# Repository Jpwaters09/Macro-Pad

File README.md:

# Macro Pad

A 12-key macro pad with a configurable rotary encoder and OLED display, built around the RP2354A microcontroller and custom MicroPython firmware. Fully programmable through a web-based configurator.

##

<div style="display: flex">

</div>

##

## How to Use
Plug the Macro Pad into your Windows, Linux, or macOS device using a USB-C data cable, then go to the [Installation Website](https://macropad.jpwaters09.com/Install%20or%20Update) and follow the steps to install (or update) the Macro Pad firmware. This requires a browser that supports Web Serial (Chrome, Edge, Opera, or Firefox), Safari isn't supported.

The OLED display shows the current layer and the function assigned to each key. Press and hold the rotary encoder button to switch layers.

To configure the device (adding, editing, or deleting layers) visit the [Macro Pad Programmer](https://macropad.jpwaters09.com/Configurator).

## Coming Soon
 - A Windows app that will allow you to update and configure settings for the Macro Pad.

## Why I Made This
I built this project to create a fully customisable and open-sourced macro pad. It has also served as a way to develop my skills in schematic design, PCB layout, and 3D Modelling.

## Features
 - USB C
 - 12 macro buttons
 - Rotary encoder with button
 - 128 x 64 OLED display
 - 3D printable housing
 - RP2354A microcontroller
 - 2MB internal flash storage
 - Custom Micropython firmware
 - Multiple programmable layers
 - Web-based configurator (no software install)
 - USB HID compliant (works instantly on any OS)

## Bill Of Materials
|Item                  |Description                                                            |Quantity|Unit Price (£)|Total Price (£) Inc. Tax|URL                                                  |
|----------------------|-----------------------------------------------------------------------|--------|--------------|------------------------|-----------------------------------------------------|
|CL05A104KA5NNNC       |100nF ±10% 25V Ceramic Capacitor X5R 0402                              |100     |$0.0016       |$0.16                   |https://www.lcsc.com/product-detail/C100072.html     |
|CC0402KRX5R5BB103     |10nF ±10% 6.3V Ceramic Capacitor X5R 0402                              |100     |$0.0012       |$0.12                   |https://www.lcsc.com/product-detail/C1853984.html    |
|HGC0805R7106K250NSLJ  |10uF ±10% 25V Ceramic Capacitor X7R 0805                               |5       |$0.1585       |$0.79                   |https://www.lcsc.com/product-detail/C33546010.html       |
|ABM8-272-T3           |±30ppm 10pF ±30ppm SMD3225-4P Crystals RoHS                            |5       |$0.2902       |$1.45                   |https://www.lcsc.com/product-detail/C20625731.html   |
|CL05C150JB5NNNC       |15pF ±5% 50V Ceramic Capacitor C0G 0402                                |100     |$0.0036       |$0.36                   |https://www.lcsc.com/product-detail/C86285.html      |
|FRC0402J102 TS        |1kΩ 62.5mW 50V Thick Film Resistor ±100ppm/℃ ±5% 0402 Chip Resistor   |100     |$0.0008       |$0.08                   |https://www.lcsc.com/product-detail/C2906899.html    |
|RC0402FR-0727RL       |27Ω ±1% 62.5mW 0402 Thick Film Resistor                                |100     |$0.0008       |$0.08                   |https://www.lcsc.com/product-detail/C138021.html     |
|AOTA-B201610S3R3-101-T|2.1A 3.3uH 115mΩ 2.4A Molded Inductor 0806 Fixed Inductors RoHS        |5       |$0.2888       |$1.44                   |https://www.lcsc.com/product-detail/C42411119.html   |
|RAT0233R0FTH          |62.5mW 33Ω 50V Thick Film Resistor ±100ppm/℃ ±1% 0402 Chip Resistor   |100     |$0.0015       |$0.15                   |https://www.lcsc.com/product-detail/C5139599.html    |
|CL05A475KQ5NRNC       |4.7uF ±10% 6.3V Ceramic Capacitor X5R 0402                             |100     |$0.0060       |$0.60                   |https://www.lcsc.com/product-detail/C2932473.html    |
|1RC0402F5101          |5.1kΩ ±1% 62.5mW 0402 Thick Film Resistor                              |100     |$0.0009       |$0.09                   |https://www.lcsc.com/product-detail/C53224182.html   |
|NCP1117ST33T3G        |Linear Voltage Regulator IC Positive Fixed 1 Output 1A SOT-223         |5       |$0.2615       |$1.31                   |https://www.lcsc.com/product-detail/C26537.html      |
|PZ254V-11-04P         |Pin Header 4 Position 2.54mm Pitch Single Row Through Hole -40℃~+105℃|20      |$0.0236       |$0.47                   |https://www.lcsc.com/product-detail/C2691448.html    |
|Rotary Encoder Knob   |22x12mm 6mm D-Type Shaft Hole Knob                                     |1       |$1.6500       |$1.65                   |https://www.aliexpress.com/item/1005011592374989.html|
|SSD1306               |128x64 I2C OLED Display                                                |1       |$0.9900       |$0.99                   |https://www.aliexpress.com/item/1005008995931139.html|
|PEC11R-4225F-S0024    |Plugin Encoders RoHS                                                   |1       |$1.8539       |$1.85                   |https://www.lcsc.com/product-detail/C18198884.html   |
|Cherry MX Keycaps     |Blank black keycap for Cherry MX switches                              |20      |$0.1500       |$3.00                   |https://www.aliexpress.com/item/1005007572331245.html|
|Cherry MX Red Switch  |Cherry MX red 3-pin linear switches                                    |16      |$0.65         |$10.43                  |https://www.aliexpress.com/item/4000100166477.html   |
|RP2354A               |QFN-60(7x7) Microcontrollers RoHS                                      |1       |$1.4615       |$1.46                   |https://www.lcsc.com/product-detail/C41378174.html   |
|2171790001            |USB 2.0 5A 1 16P -40℃~+85℃ SMD USB Connector Assemblies RoHS         |1       |$0.6229       |$0.62                   |https://www.lcsc.com/product-detail/C3197684.html    |

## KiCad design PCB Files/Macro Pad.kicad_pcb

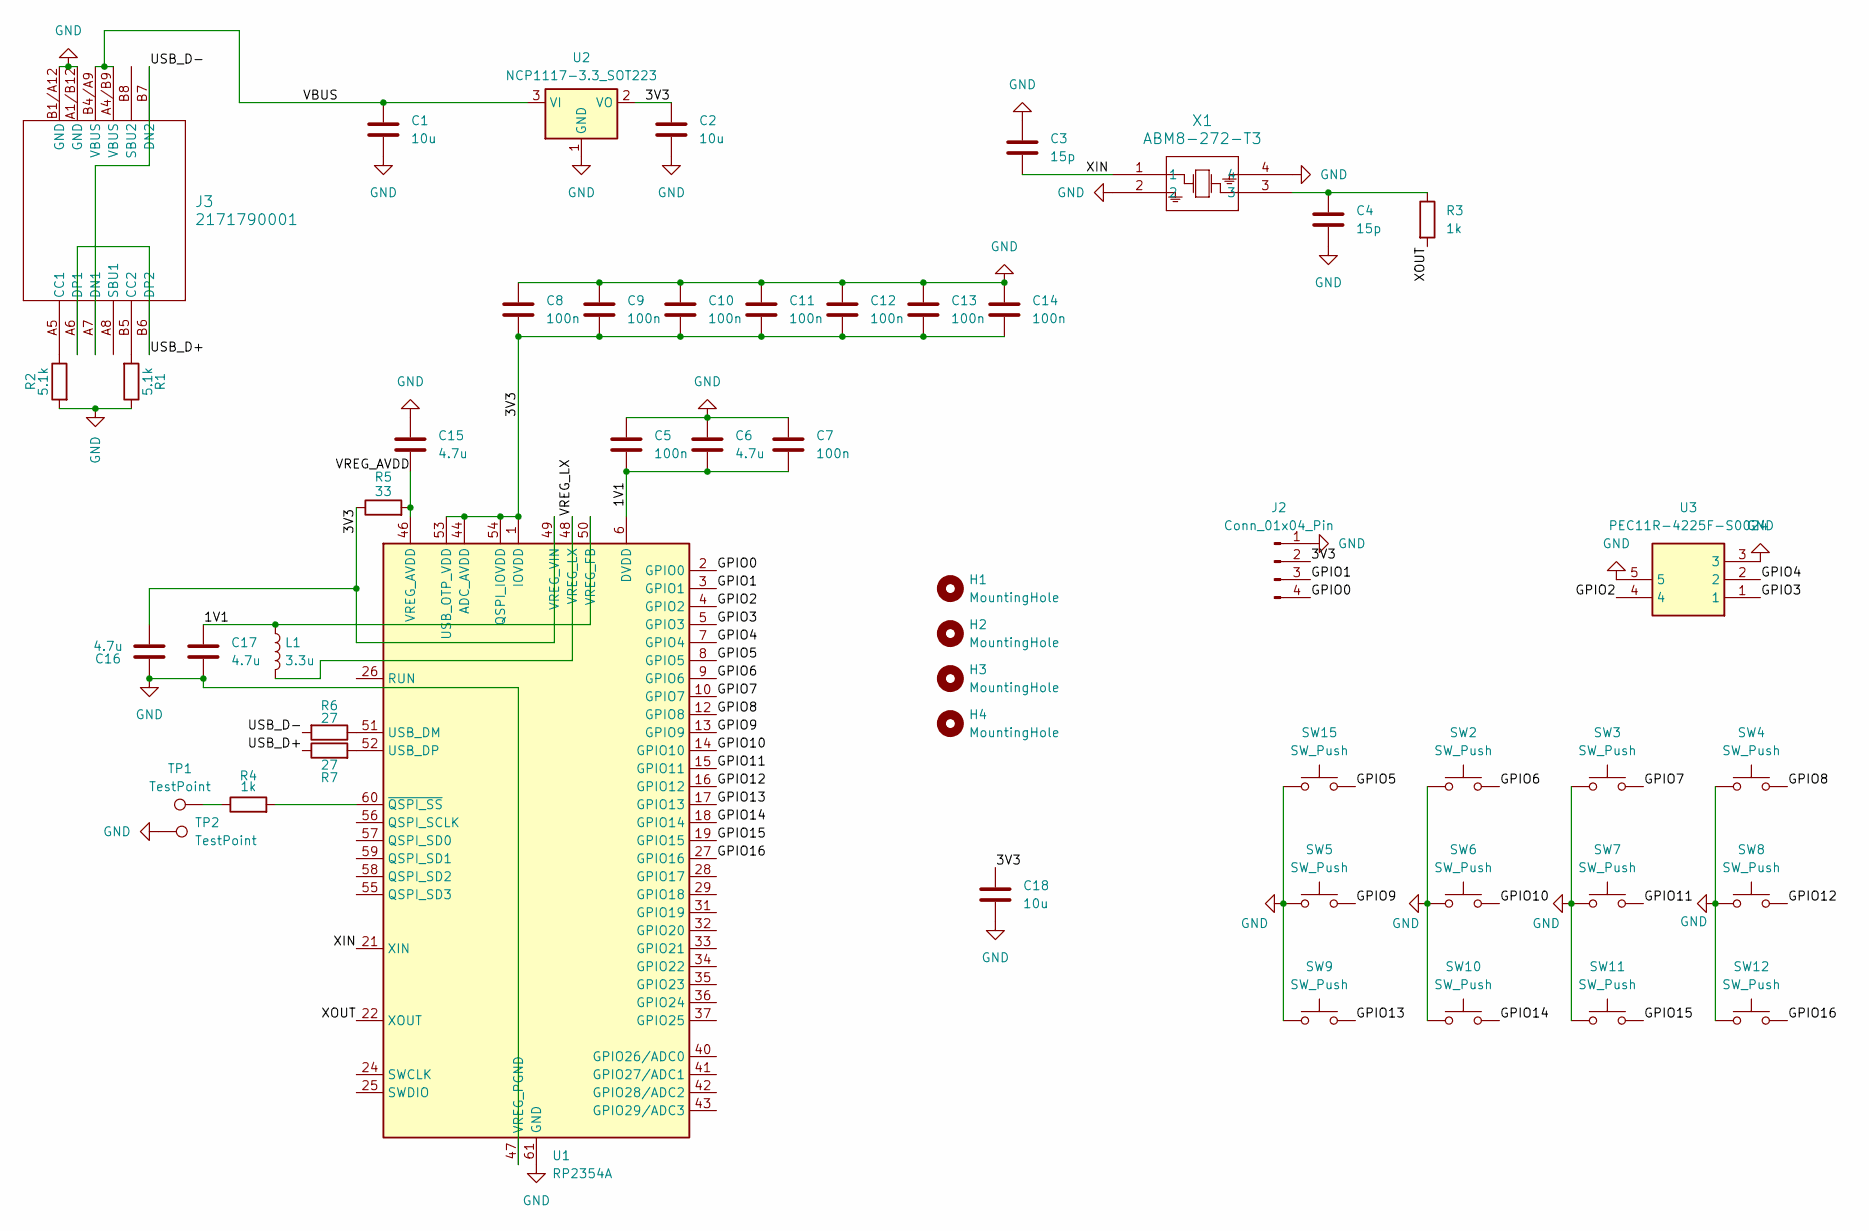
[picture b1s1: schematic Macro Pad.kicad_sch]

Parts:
C1, C2: 10u; C_0805_2012Metric
C3, C4: 15p; C_0402_1005Metric
C5, C7, C8, C9, C10, C11, C12, C13, C14: 100n; C_0402_1005Metric
C6, C15, C16, C17: 4.7u; C_0402_1005Metric
C18: 10u; C_0402_1005Metric
H1, H2, H3, H4: MountingHole; MountingHole_5mm
J2: Conn_01x04_Pin; PinHeader_1x04_P2.54mm_Vertical
J3: 2171790001; 2171790001_MOL
L1: 3.3u; AOTAB201610S3R3101T
R1, R2: 5.1k; C_0402_1005Metric
R3, R4: 1k; C_0402_1005Metric
R5: 33; C_0402_1005Metric
R6, R7: 27; C_0402_1005Metric
SW2, SW3, SW4, SW5, SW6, SW7, SW8, SW9, SW10, SW11, SW12, SW15: SW_Push; SW_Cherry_MX_1.00u_PCB
TP1, TP2: TestPoint; TestPoint_Pad_2.0x2.0mm
U1: RP2354A; QFN-60-1EP_7x7mm_P0.4mm_EP3.4x3.4mm
U2: NCP1117-3.3_SOT223; SOT-223-3_TabPin2
U3: PEC11R-4225F-S0024; Manufacturer_Part_Number PEC11R-4225F-S0024; Mouser Part Number 652-PEC11R-4225F-S24
X1: ABM8-272-T3; ABM8-272-T3_ABR

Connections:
/1V1: C5.2, C6.2, C7.2, C17.1, L1.1, U1.6 (DVDD), U1.23 (DVDD), U1.39 (DVDD), U1.50 (VREG_FB)
/3V3: C2.1, C8.2, C9.2, C10.2, C11.2, C12.2, C13.2, C14.2, C16.2, C18.1, J2.2, R5.1, U1.1 (IOVDD), U1.11 (IOVDD), U1.20 (IOVDD), U1.30 (IOVDD), U1.38 (IOVDD), U1.44 (ADC_AVDD), U1.45 (IOVDD), U1.49 (VREG_VIN), U1.53 (USB_OTP_VDD), U1.54 (QSPI_IOVDD), U2.2 (VO)
/GPIO0: J2.4, U1.2 (GPIO0)
/GPIO1: J2.3, U1.3 (GPIO1)
/GPIO2: U1.4 (GPIO2), U3.4
/GPIO3: U1.5 (GPIO3), U3.1
/GPIO4: U1.7 (GPIO4), U3.2
/GPIO5: SW15.2, U1.8 (GPIO5)
/GPIO6: SW2.2, U1.9 (GPIO6)
/GPIO7: SW3.2, U1.10 (GPIO7)
/GPIO8: SW4.2, U1.12 (GPIO8)
/GPIO9: SW5.2, U1.13 (GPIO9)
/GPIO10: SW6.2, U1.14 (GPIO10)
/GPIO11: SW7.2, U1.15 (GPIO11)
/GPIO12: SW8.2, U1.16 (GPIO12)
/GPIO13: SW9.2, U1.17 (GPIO13)
/GPIO14: SW10.2, U1.18 (GPIO14)
/GPIO15: SW11.2, U1.19 (GPIO15)
/GPIO16: SW12.2, U1.27 (GPIO16)
/USB_D+: J3.A6 (DP1), J3.B6 (DP2), R7.1
/USB_D-: J3.A7 (DN1), J3.B7 (DN2), R6.2
/VBUS: C1.1, J3.A4/B9 (VBUS), J3.B4/A9 (VBUS), U2.3 (VI)
/VREG_AVDD: C15.2, R5.2, U1.46 (VREG_AVDD)
/VREG_LX: L1.2, U1.48 (VREG_LX)
/XIN: C3.1, U1.21 (XIN), X1.1
/XOUT: R3.2, U1.22 (XOUT)
GND: C1.2, C2.2, C3.2, C4.2, C5.1, C6.1, C7.1, C8.1, C9.1, C10.1, C11.1, C12.1, C13.1, C14.1, C15.1, C16.1, C17.2, C18.2, J2.1, J3.A1/B12 (GND), J3.B1/A12 (GND), R1.1, R2.2, SW2.1, SW3.1, SW4.1, SW5.1, SW6.1, SW7.1, SW8.1, SW9.1, SW10.1, SW11.1, SW12.1, SW15.1, TP2.1, U1.47 (VREG_PGND), U1.61 (GND), U2.1 (GND), U3.3, U3.5, X1.2, X1.4
unnamed: C4.1, R3.1, X1.3
unnamed: J3.A5 (CC1), R2.1
unnamed: J3.B5 (CC2), R1.2
unnamed: R4.1, TP1.1
unnamed: R6.1, U1.51 (USB_DM)
unnamed: R7.2, U1.52 (USB_DP)
unnamed: R4.2, U1.60 (~QSPI_SS)

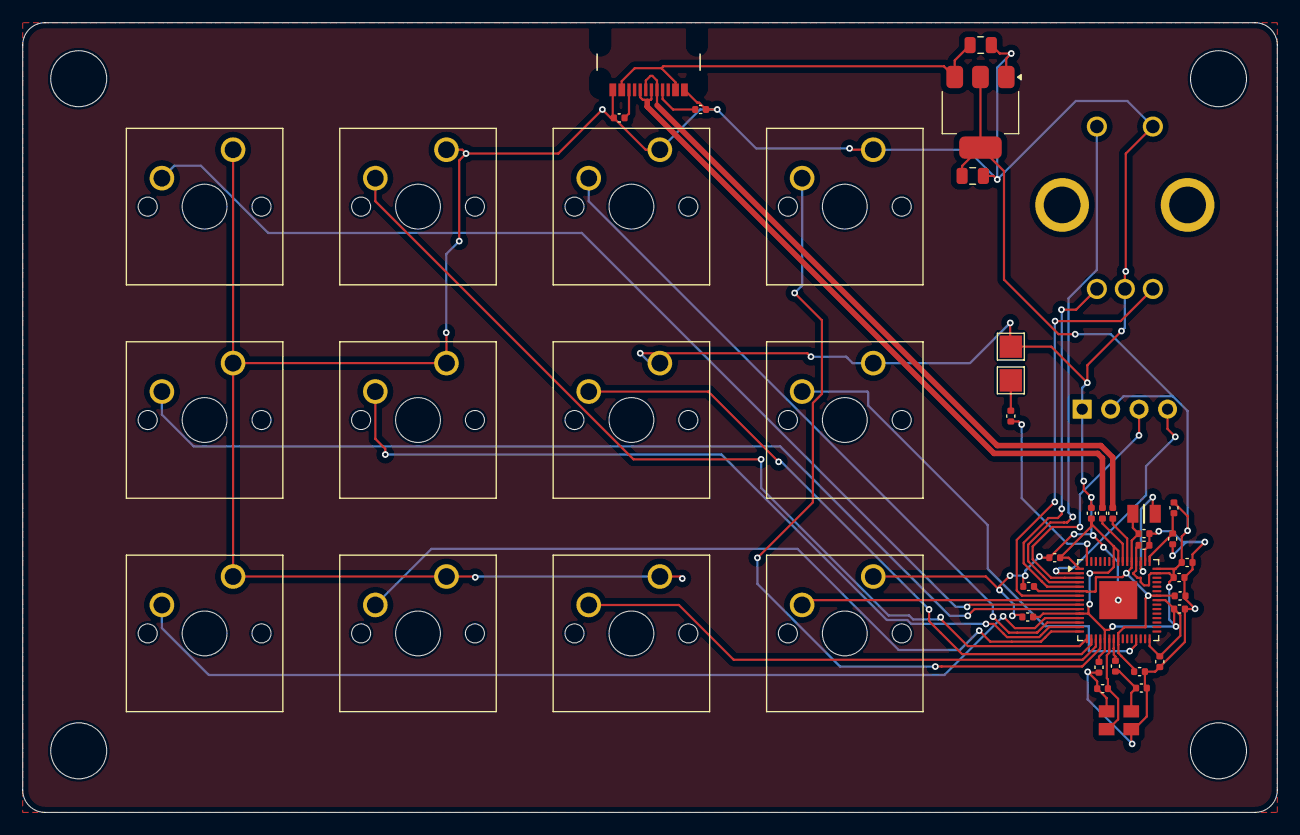
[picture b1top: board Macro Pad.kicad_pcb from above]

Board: 2 copper layers, 112.0 x 70.5 mm, 50 parts (0 on the bottom side), 34 nets.

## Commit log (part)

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2026-03-18 Enhance README with usage and project details
    Expanded the README with usage instructions and project motivation.
2026-03-18 Edited
2026-03-18 Change image layout to flexbox in README
    Updated image display format to use a flexbox layout.
2026-03-18 Update Macro Pad BOM with new item entries
2026-03-18 Add Bill of Materials to README
    Added a Bill of Materials section with detailed item descriptions, quantities, prices, and URLs for sourcing components.
2026-03-19 Update Macro Pad BOM with additional components
2026-03-21 Added
2026-03-21 Revise README content and structure
    Updated README for clarity and formatting improvements.
2026-03-22 Fix pricing format in component list
    Updated pricing format for Cherry MX Keycap and SSD1306 display.
2026-03-22 Fix resistor power rating in README
2026-03-22 Update Macro Pad BOM with new items
2026-03-26 Revise Bill of Materials with updated pricing
    Updated the Bill of Materials section with new item prices and URLs.
2026-04-02 Revise Bill Of Materials with new items
    Updated Bill Of Materials with new components and prices.
2026-06-22 Update quantity for Cherry MX Red Switch in README
2026-06-22 Revise Macro Pad BOM with updated component details
    Updated quantities and URLs for several components.
2026-06-22 Modify Cherry MX Red Switch details in README
    Updated the quantity and price for Cherry MX Red Switch.
2026-06-22 Update Macro Pad BOM with new item formatting

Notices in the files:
PCB Files/Macro Pad.kicad_pcb:
Copyright © 2026 Jacob Waters
